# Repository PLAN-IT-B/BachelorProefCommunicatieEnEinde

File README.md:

# BachlorProef: Communicatie en einde.
Repository van Henri Vandeputte

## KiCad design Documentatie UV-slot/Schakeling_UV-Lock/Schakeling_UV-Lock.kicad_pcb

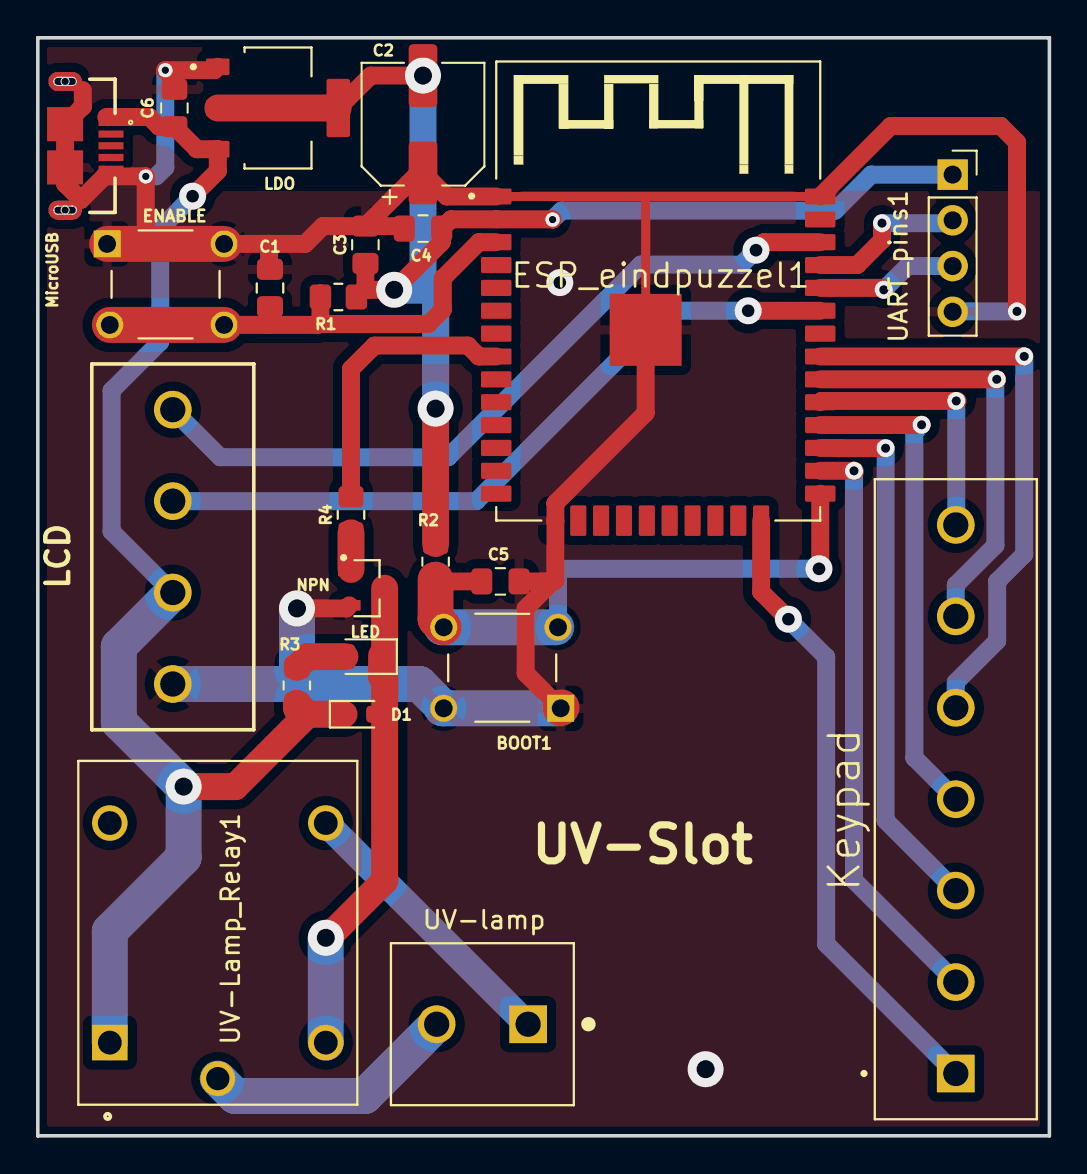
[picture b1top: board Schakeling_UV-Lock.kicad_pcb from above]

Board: 2 copper layers, 56.2 x 61.0 mm, 23 parts (0 on the bottom side), 22 nets.

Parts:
BOOT1: SW_Push; TE_3-1825910-1
C1, C4, C5: 0.1u; C_0805_2012Metric_Pad1.18x1.45mm_HandSolder
C2: 220u; CP_Elec_6.3x7.7
C3: 22u; C_0805_2012Metric_Pad1.18x1.45mm_HandSolder
C6: 10u; C_0805_2012Metric_Pad1.18x1.45mm_HandSolder
D1: D; LED_0603_1608Metric_Pad1.05x0.95mm_HandSolder
ENABLE: SW_Push; TE_3-1825910-1
ESP_eindpuzzel1: ESP-WROOM-32; MODULE_ESP-WROOM-32
Keypad: 282841-7; TE_282841-7
LCD: 282841-4; 2828414
LDO: AMS1117; SOT229P700X180-4N
LED: LED; LED_0805_2012Metric_Pad1.15x1.40mm_HandSolder
MicroUSB: USB3090-XX-X_REVE; GCT_USB3090-XX-X_REVE
NPN: BC817; SOT95P230X110-3N
R1, R2: 10k; R_0805_2012Metric_Pad1.20x1.40mm_HandSolder
R3, R4: 1k; R_0805_2012Metric_Pad1.20x1.40mm_HandSolder
UART_pins1: Conn_01x04_Female; PinSocket_1x04_P2.54mm_Vertical
UV-Lamp_Relay1: SRD-05VDC-SL-C; RELAY_SRD-05VDC-SL-C
UV-lamp: 282841-2; TE_282841-2

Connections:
3.3V: C2.2, C3.2, C4.2, ESP_eindpuzzel1.2 (3V3), LDO.2 (VOUT), LDO.4 (VOUT), R1.2, R2.1, UART_pins1.1
5V: C6.1, D1.1 (K), LCD.2, LDO.3 (VIN), MicroUSB.1 (VBUS), R3.1, UV-Lamp_Relay1.A1
GND: BOOT1.1, BOOT1.2, C1.1, C2.1, C3.1, C4.1, C5.1, C6.2, ENABLE.1, ENABLE.2, ESP_eindpuzzel1.1 (GND), ESP_eindpuzzel1.1.1 (GND), ESP_eindpuzzel1.15 (GND), ESP_eindpuzzel1.38 (GND), LCD.1, LDO.1 (ADJ/GND), MicroUSB.5 (GND), MicroUSB.6 (SHIELD), MicroUSB.7 (SHIELD), MicroUSB.8 (SHIELD), MicroUSB.9 (SHIELD), NPN.2, UART_pins1.4
IO2: ESP_eindpuzzel1.24 (IO2), Keypad.1
IO4: ESP_eindpuzzel1.26 (IO4), Keypad.2
IO5: ESP_eindpuzzel1.29 (IO5), Keypad.7
IO16: ESP_eindpuzzel1.27 (IO16), Keypad.3
IO17: ESP_eindpuzzel1.28 (IO17), Keypad.4
IO18: ESP_eindpuzzel1.30 (IO18), Keypad.6
IO19: ESP_eindpuzzel1.31 (IO19), Keypad.5
IO21: ESP_eindpuzzel1.33 (IO21), LCD.3
IO22: ESP_eindpuzzel1.36 (IO22), LCD.4
IO32: ESP_eindpuzzel1.8 (IO32), R4.2
unnamed: C1.2, ENABLE.3, ENABLE.4, ESP_eindpuzzel1.3 (EN), R1.1
unnamed: D1.2 (A), LED.1 (K), NPN.3, UV-Lamp_Relay1.A2
unnamed: BOOT1.3, BOOT1.4, C5.2, ESP_eindpuzzel1.25 (IO0), R2.2
unnamed: NPN.1, R4.1
unnamed: LED.2 (A), R3.2
unnamed: UV-Lamp_Relay1.COM, UV-lamp.2
unnamed: UV-Lamp_Relay1.NO, UV-lamp.1
RX: ESP_eindpuzzel1.34 (RXD0), UART_pins1.3
TX: ESP_eindpuzzel1.35 (TXD0), UART_pins1.2

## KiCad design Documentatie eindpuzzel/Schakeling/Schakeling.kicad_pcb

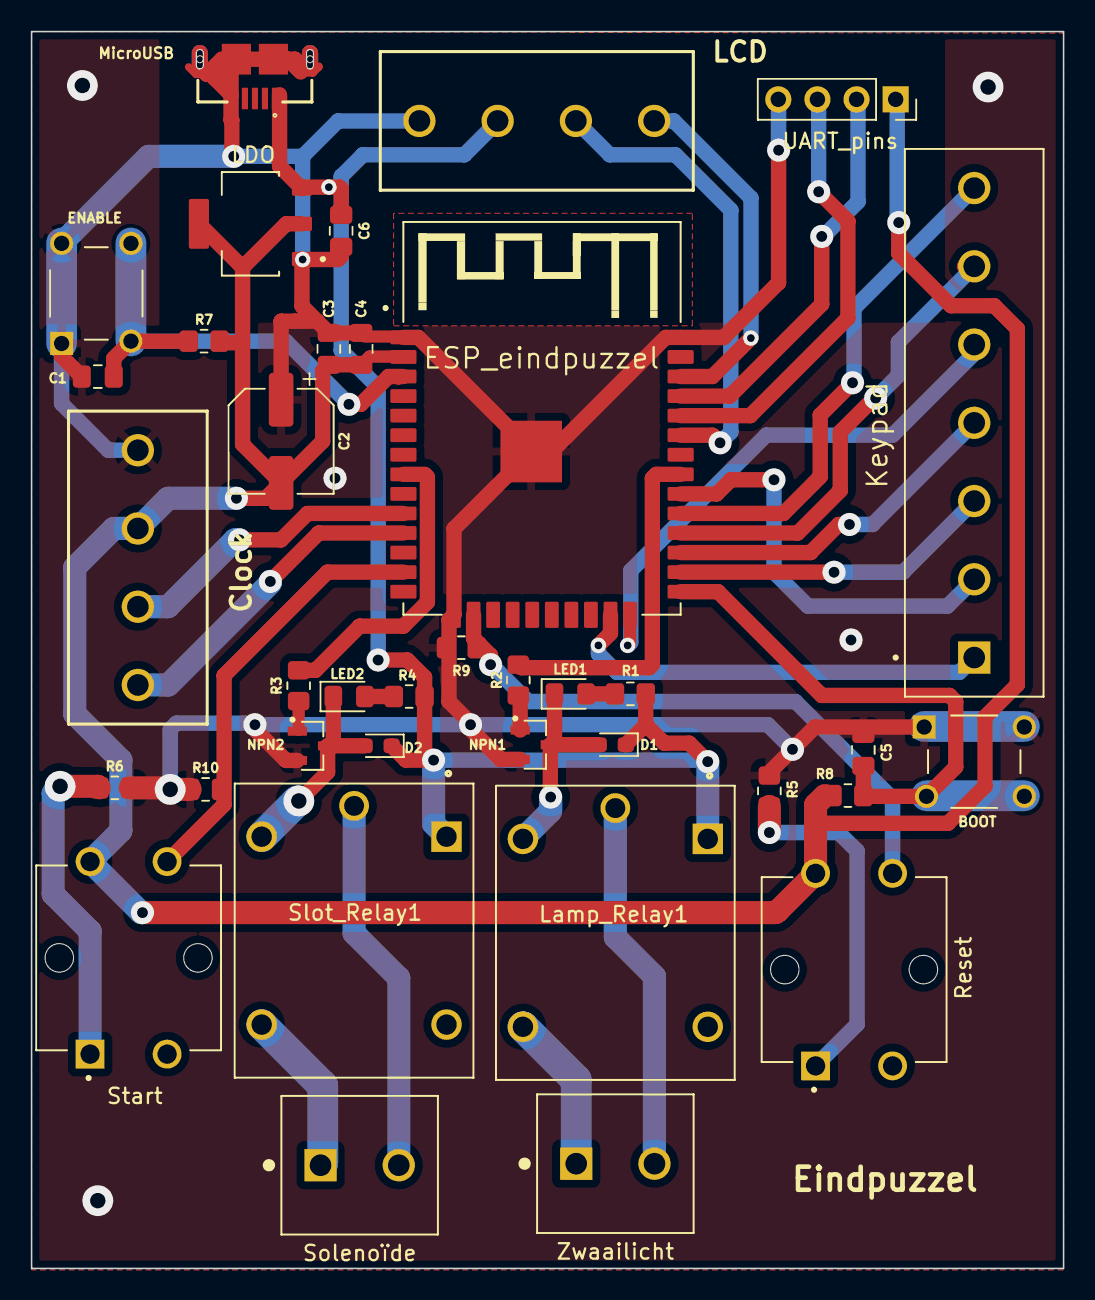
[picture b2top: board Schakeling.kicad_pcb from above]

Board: 2 copper layers, 67.0 x 80.3 mm, 37 parts (0 on the bottom side), 34 nets.

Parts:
BOOT: SW_Push; TE_3-1825910-1
C1, C4, C5: 0.1u; C_0805_2012Metric_Pad1.18x1.45mm_HandSolder
C2: 220u; CP_Elec_6.3x7.7
C3: 22u; C_0805_2012Metric_Pad1.18x1.45mm_HandSolder
C6: 10u; C_0805_2012Metric_Pad1.18x1.45mm_HandSolder
Clock: 282841-4; 2828414
D1, D2: D; LED_0603_1608Metric_Pad1.05x0.95mm_HandSolder
ENABLE: SW_Push; TE_3-1825910-1
ESP_eindpuzzel: ESP-WROOM-32; MODULE_ESP-WROOM-32
Keypad: 282841-7; TE_282841-7
LCD: 282841-4; 2828414
LDO: AMS1117; SOT229P700X180-4N
LED1, LED2: LED; LED_0805_2012Metric_Pad1.15x1.40mm_HandSolder
Lamp_Relay1: SRD-05VDC-SL-C; RELAY_SRD-05VDC-SL-C
MicroUSB: USB3090-XX-X_REVE; GCT_USB3090-XX-X_REVE
NPN1, NPN2: BC817; SOT95P230X110-3N
R1, R2, R3, R4, R5, R6, R9, R10: 1k; R_0805_2012Metric_Pad1.20x1.40mm_HandSolder
R7, R8: 10k; R_0805_2012Metric_Pad1.20x1.40mm_HandSolder
Reset: B3F-4050; SW_B3F-4050
Slot_Relay1: SRD-05VDC-SL-C; RELAY_SRD-05VDC-SL-C
Solenoïde: 282841-2; TE_282841-2
Start: B3F-4050; SW_B3F-4050
UART_pins: Conn_01x04_Female; PinSocket_1x04_P2.54mm_Vertical
Zwaailicht: 282841-2; TE_282841-2

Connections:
3.3V: C2.2, C3.2, C4.2, Clock.3, ESP_eindpuzzel.2 (3V3), LDO.2 (VOUT), LDO.4 (VOUT), R7.2, R8.1, Reset.2, Start.2, UART_pins.1
5V: C6.1, D1.1 (K), D2.1 (K), LCD.2, LDO.3 (VIN), Lamp_Relay1.A1, MicroUSB.1 (VBUS), R1.1, R4.1, Slot_Relay1.A1
GND: BOOT.1, BOOT.2, C1.1, C2.1, C3.1, C4.1, C5.1, C6.2, Clock.4, ENABLE.1, ENABLE.2, ESP_eindpuzzel.1 (GND), ESP_eindpuzzel.1.1 (GND), ESP_eindpuzzel.15 (GND), ESP_eindpuzzel.38 (GND), LCD.1, LDO.1 (ADJ/GND), MicroUSB.5 (GND), MicroUSB.6 (SHIELD), MicroUSB.7 (SHIELD), MicroUSB.8 (SHIELD), MicroUSB.9 (SHIELD), NPN1.2, NPN2.2, R5.1, R6.1, R9.1, R10.1, UART_pins.4
IO2: ESP_eindpuzzel.24 (IO2), Keypad.5
IO4: ESP_eindpuzzel.26 (IO4), Keypad.3
IO5: ESP_eindpuzzel.29 (IO5), Keypad.7
IO13: ESP_eindpuzzel.16 (IO13), R9.2, Reset.4 (A)
IO14: ESP_eindpuzzel.13 (IO14), R10.2, Start.4 (A)
IO15: ESP_eindpuzzel.23 (IO15), Keypad.1
IO16: ESP_eindpuzzel.27 (IO16), Keypad.4
IO17: ESP_eindpuzzel.28 (IO17), Keypad.6
IO18: ESP_eindpuzzel.30 (IO18), Keypad.2
IO19: ESP_eindpuzzel.31 (IO19), R2.2
IO21: ESP_eindpuzzel.33 (IO21), LCD.3
IO22: ESP_eindpuzzel.36 (IO22), LCD.4
IO25: Clock.2, ESP_eindpuzzel.10 (IO25)
IO26: Clock.1, ESP_eindpuzzel.11 (IO26)
IO32: ESP_eindpuzzel.8 (IO32), R3.2
unnamed: C1.2, ENABLE.3, ENABLE.4, ESP_eindpuzzel.3 (EN), R7.1
unnamed: D1.2 (A), LED1.1 (K), Lamp_Relay1.A2, NPN1.3
unnamed: D2.2 (A), LED2.1 (K), NPN2.3, Slot_Relay1.A2
unnamed: BOOT.3, BOOT.4, C5.2, ESP_eindpuzzel.25 (IO0), R8.2
unnamed: LED1.2 (A), R1.2
unnamed: LED2.2 (A), R4.2
unnamed: Lamp_Relay1.COM, Zwaailicht.2
unnamed: Lamp_Relay1.NO, Zwaailicht.1
unnamed: NPN1.1, R2.1
unnamed: NPN2.1, R3.1
unnamed: R5.2, Reset.1
unnamed: R6.2, Start.1
unnamed: Slot_Relay1.COM, Solenoïde.2
unnamed: Slot_Relay1.NO, Solenoïde.1
RX: ESP_eindpuzzel.34 (RXD0), UART_pins.3
TX: ESP_eindpuzzel.35 (TXD0), UART_pins.2

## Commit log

2022-02-26 Mijn repository klaarmaken voor gebruik
2022-02-26 Blokschema's gemaakt
2022-02-26 Bestanden verplaatst van folder
2022-02-26 Blokschema's vervangen door .png files
2022-02-26 Implementatie afgewerkt
2022-02-28 Begin cijferslot code
2022-03-08 Veel updates, adds en removes
2022-03-08 andere naam
2022-03-08 Basic MQTT connection opgezet
2022-03-15 Ganze dag werk
2022-03-22 Veel betere code! + timer
2022-03-22 Kuisen van de repository, updaten van logboek en componenten lijst
2022-03-22 Kleine herschikking
2022-03-22 Kleine herschiking
2022-03-29 Kicad en code updates
2022-04-07 PCB design files en veel meer
2022-04-07 Updates pcb eindpuzzel
2022-04-13 Veel nieuwe aanpassing in de Kicad files ( en ook een paar in de code)
2022-04-13 Wifi antennes extra ruimte gegeven
2022-04-16 Finale design PCB's
2022-04-19 Updates van alles
2022-04-19 aanpassingen voor publishen buffer
2022-04-19 4-cijfer code
2022-04-19 affiches/brochures toegevoegd
2022-04-26 Updates en afwerking UV-slot code
2022-04-26 Updates in UV-slot code
2022-04-26 Solidworks bestanden UV-slot toegevoegd
2022-05-02 LaserCut bestanden, UV-slot code en Datacommunicatie update
2022-05-02 Updatec UV-slot code
2022-05-03 Eindpuzzel code, UV slot code
2022-05-06 Solidworks puzzelBox(en) :/
2022-05-17 Structuur en bug fixes
2022-05-18 UV-slot samenwerking met buffer
2022-05-18 Bug fix
2022-05-18 Eindslot code aangepast voor samenwerking met buffer en samenwerking met wristbands
2022-05-18 schematic geplot van eindpuzzel pcb
2022-05-18 Info schematic geupdate en svg files geplot
2022-05-18 svg files updates
2022-05-18 3D-view pcb's toegevoegd
2022-05-19 bug fixes beide codes
2022-05-19 Werkende versie van UV-slot in communicatie met buffer
2022-05-19 Bug fixes en EINDCODE
2022-05-19 UV-slot code opgekuisd en klaar voor verslag.
2022-05-19 Super cleane code voor zowel UV-slot als eindpuzzel
2022-05-20 Betere structuur
2022-05-21 Naam veranderd van basic mqqt connection
2022-05-21 Mooiere flowcharts en oude flowcharts weg
2022-05-21 yeah
2022-05-22 STL files toegevoegd
2022-05-23 Laatste update
2022-05-23 betere reset start flowchart
